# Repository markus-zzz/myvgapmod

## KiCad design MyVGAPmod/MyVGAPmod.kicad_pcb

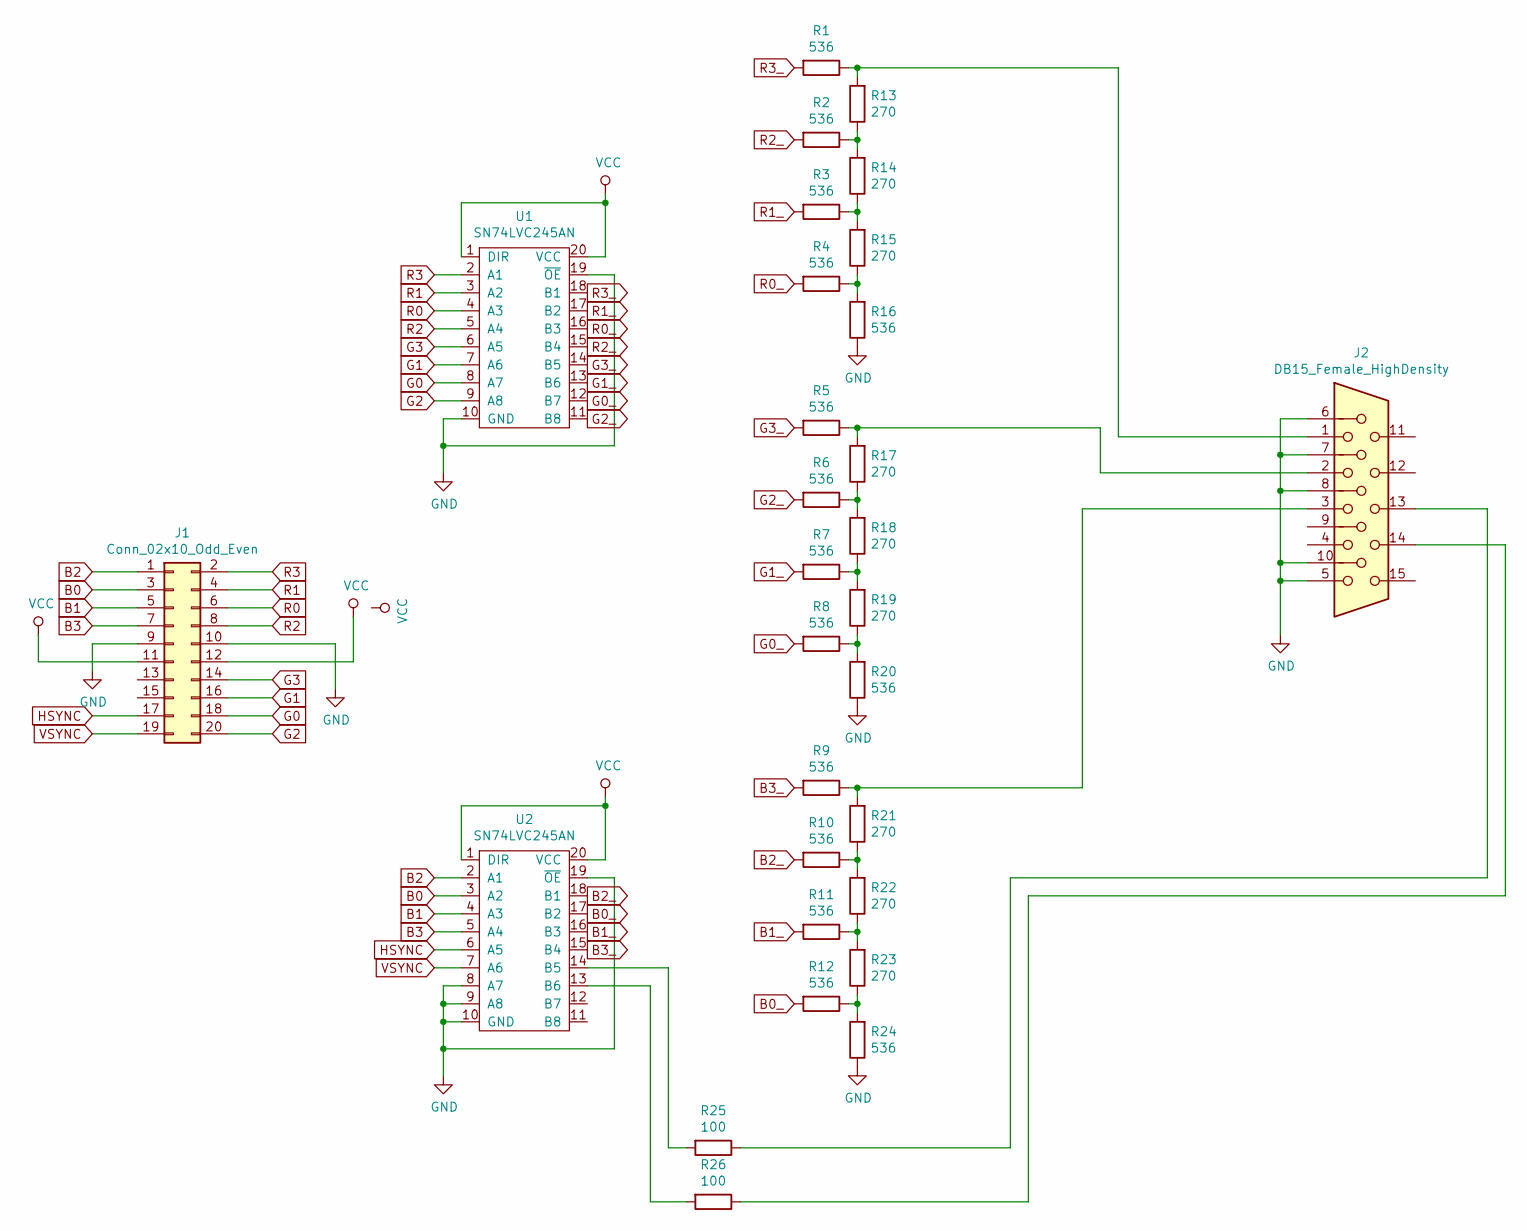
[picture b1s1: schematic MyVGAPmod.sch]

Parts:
J1: Conn_02x10_Odd_Even; PinSocket_2x10_P2.54mm_Vertical
J2: DB15_Female_HighDensity; DSUB-15-HD_Female_Horizontal_P2.29x1.98mm_EdgePinOffset3.03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
R1, R2, R3, R4, R5, R6, R7, R8, R9, R10, R11, R12, R16, R20, R24: 536; R_Axial_DIN0204_L3.6mm_D1.6mm_P7.62mm_Horizontal
R13, R14, R15, R17, R18, R19, R21, R22, R23: 270; R_Axial_DIN0204_L3.6mm_D1.6mm_P7.62mm_Horizontal
R25, R26: 100; R_Axial_DIN0204_L3.6mm_D1.6mm_P7.62mm_Horizontal
U1, U2: SN74LVC245AN; DIP-20_W7.62mm

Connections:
B0: J1.3, U2.3 (A2)
B0_: R12.2, U2.17 (B2)
B1: J1.5, U2.4 (A3)
B1_: R11.2, U2.16 (B3)
B2: J1.1, U2.2 (A1)
B2_: R10.2, U2.18 (B1)
B3: J1.7, U2.5 (A4)
B3_: R9.2, U2.15 (B4)
G0: J1.18, U1.8 (A7)
G0_: R8.2, U1.12 (B7)
G1: J1.16, U1.7 (A6)
G1_: R7.2, U1.13 (B6)
G2: J1.20, U1.9 (A8)
G2_: R6.2, U1.11 (B8)
G3: J1.14, U1.6 (A5)
G3_: R5.2, U1.14 (B5)
GND: J1.9, J1.10, J2.5, J2.6, J2.7, J2.8, J2.10, R16.1, R20.1, R24.1, U1.10 (GND), U1.19 (~OE), U2.8 (A7), U2.9 (A8), U2.10 (GND), U2.19 (~OE)
HSYNC: J1.17, U2.6 (A5)
unnamed: J2.1, R1.1, R13.2
unnamed: J2.2, R5.1, R17.2
unnamed: J2.3, R9.1, R21.2
unnamed: J2.13, R25.1
unnamed: J2.14, R26.1
unnamed: R10.1, R21.1, R22.2
unnamed: R11.1, R22.1, R23.2
unnamed: R12.1, R23.1, R24.2
unnamed: R2.1, R13.1, R14.2
unnamed: R3.1, R14.1, R15.2
unnamed: R4.1, R15.1, R16.2
unnamed: R6.1, R17.1, R18.2
unnamed: R7.1, R18.1, R19.2
unnamed: R8.1, R19.1, R20.2
unnamed: R25.2, U2.14 (B5)
unnamed: R26.2, U2.13 (B6)
R0: J1.6, U1.4 (A3)
R0_: R4.2, U1.16 (B3)
R1: J1.4, U1.3 (A2)
R1_: R3.2, U1.17 (B2)
R2: J1.8, U1.5 (A4)
R2_: R2.2, U1.15 (B4)
R3: J1.2, U1.2 (A1)
R3_: R1.2, U1.18 (B1)
VCC: J1.11, J1.12, U1.1 (DIR), U1.20 (VCC), U2.1 (DIR), U2.20 (VCC)
VSYNC: J1.19, U2.7 (A6)

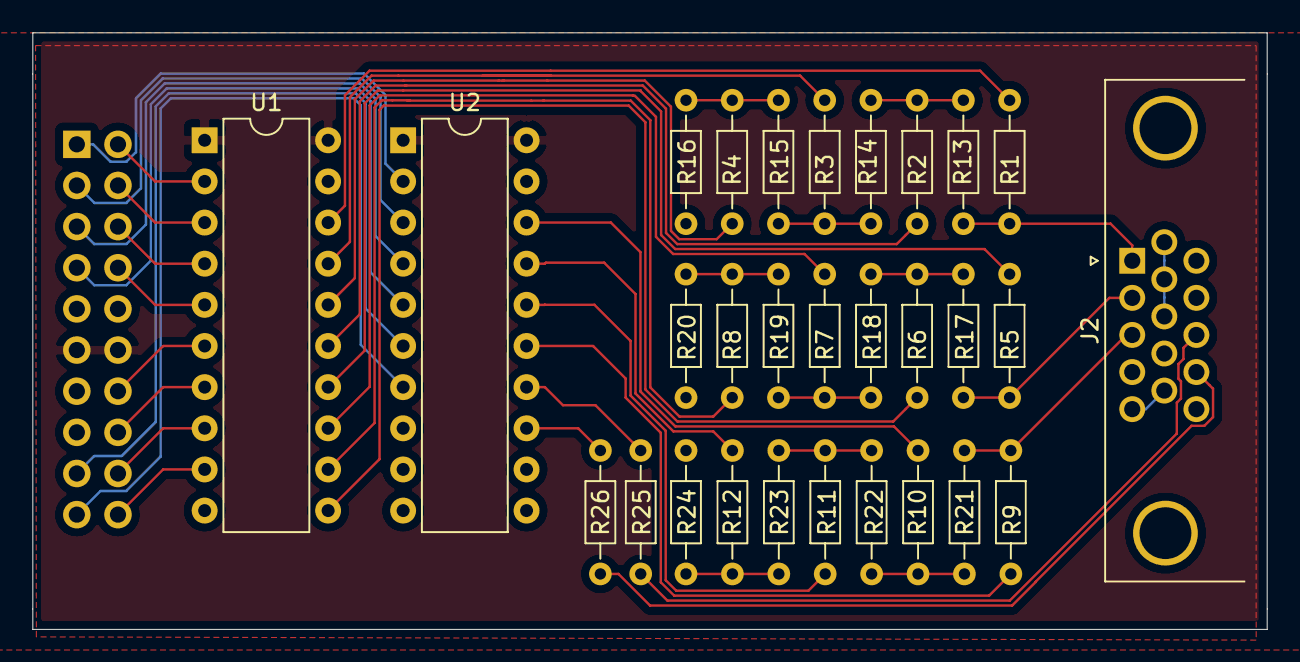
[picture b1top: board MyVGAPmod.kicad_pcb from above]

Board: 2 copper layers, 76.2 x 36.8 mm, 30 parts (1 on the bottom side), 44 nets.

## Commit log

2019-09-01 VGA PMod layout.
2019-09-01 Added screenshots and schematics pdf.
